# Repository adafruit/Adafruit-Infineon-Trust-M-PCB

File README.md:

## Adafruit Infineon Trust M Breakout Board PCB

<a href="http://www.adafruit.com/products/4351"><br/>
Click here to purchase one from the Adafruit shop</a>

PCB files for the Adafruit Infineon Trust M Breakout Board. 

Format is EagleCAD schematic and board layout
* https://www.adafruit.com/product/4351

### Description

This is a STEMMA I2C breakout for the Infineon OPTIGA TRUST M SLS 32AIA.

OPTIGA Trust M is the next generation of Trust X. OPTIGA Trust M brings RSA 1K/2K + ECC256/384.

A crypto authentication chip much like the ATECC608 STEMMA we put into the shop last week, but with: ECC NIST P256/P384, SHA-256, TRNG, DRNG, RSA® 1024/2048 and 4.5K of user memory.

This chip can store your private keys securely, as well as generate true random numbers, which is what we’ve got going on in this demo below. Check out https://github.com/Infineon/optiga-trust-m for the Arduino library

Comes with a bit of 0.1" standard header in case you want to use it with a breadboard or perfboard.  Four 2.5mm (0.1") mounting holes for easy attachment. Clear Padlock and STEMMA QT cable not included (but we have them in the shop). One board per order.

### License

Adafruit invests time and resources providing this open source design, please support Adafruit and open-source hardware by purchasing products from [Adafruit](https://www.adafruit.com)!

Designed by Limor Fried/Ladyada for Adafruit Industries.

Creative Commons Attribution/Share-Alike, all text above must be included in any redistribution. 
See license.txt for additional details.

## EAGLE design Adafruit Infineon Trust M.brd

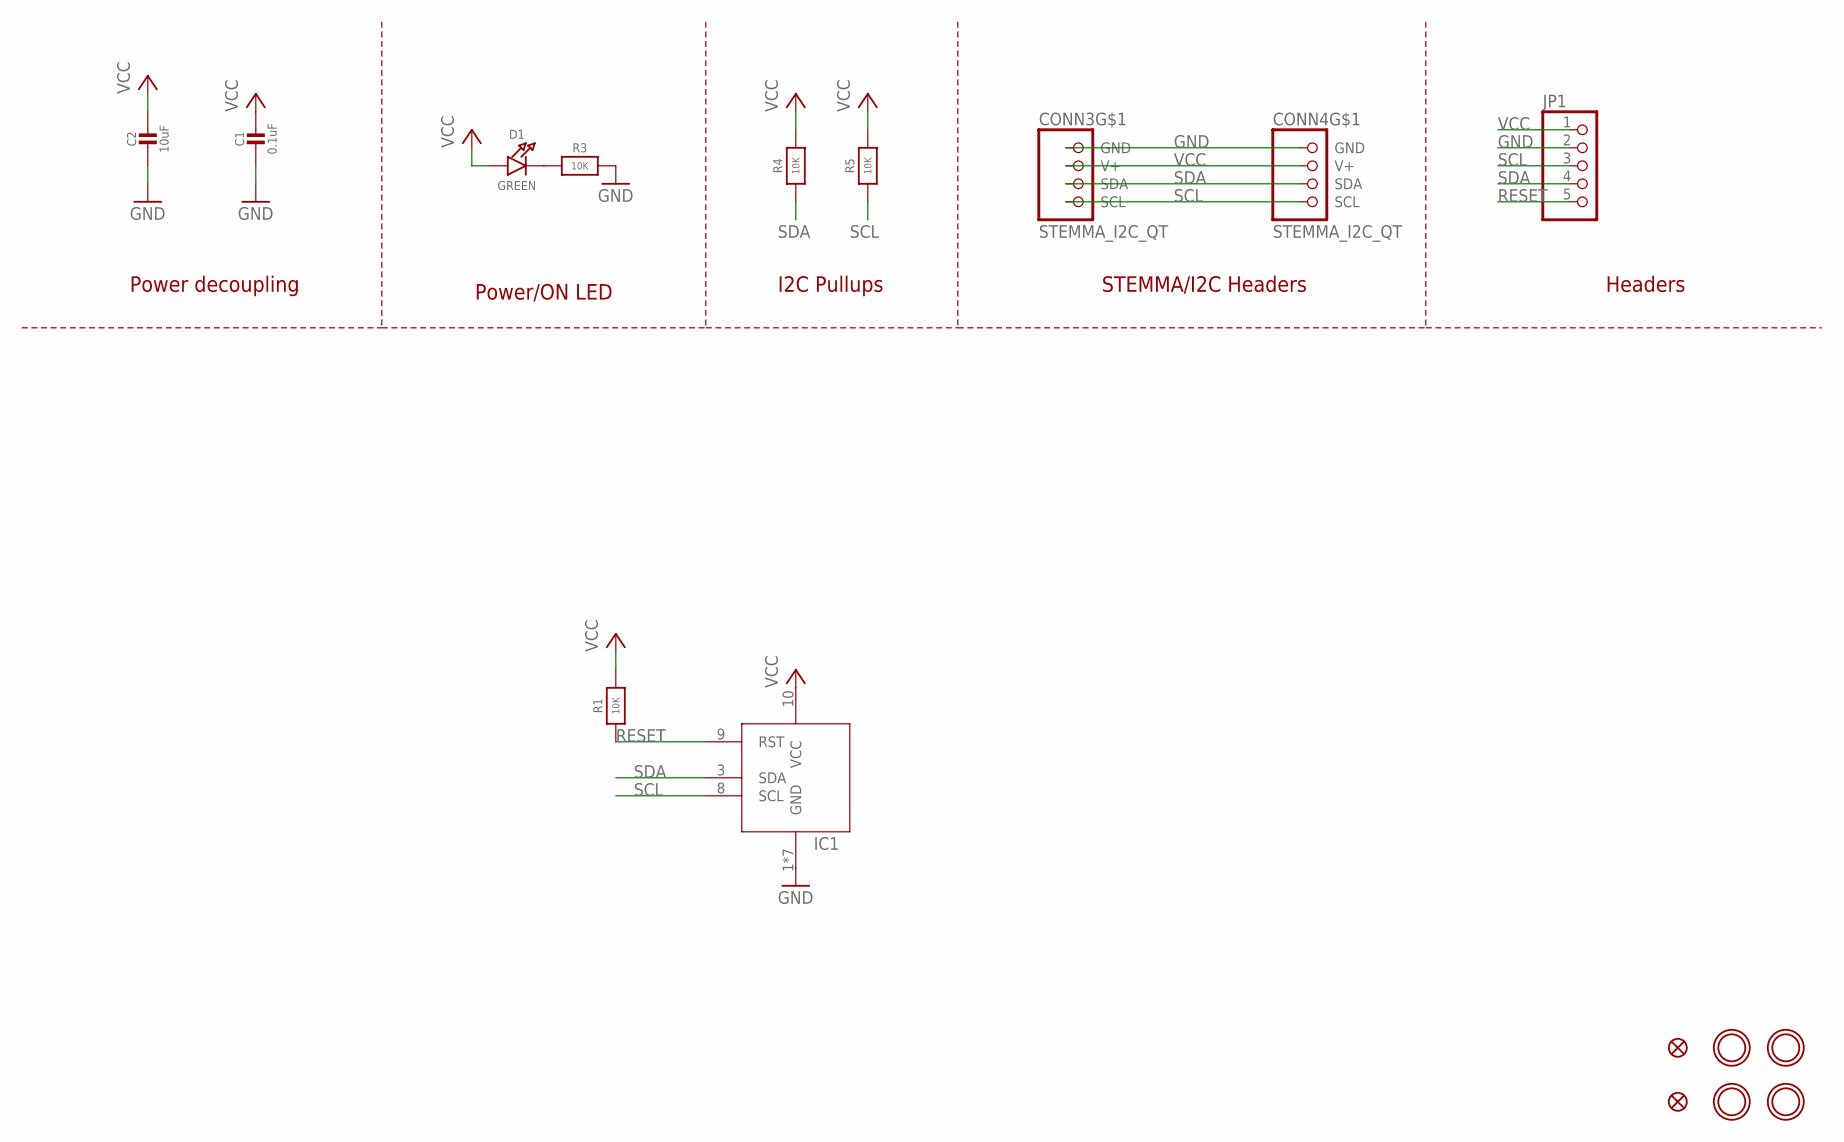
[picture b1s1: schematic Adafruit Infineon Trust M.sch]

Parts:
C1: 0.1uF; 0603-NO
C2: 10uF; 0805-NO
CONN3, CONN4: STEMMA_I2C_QT; JST_SH4
D1: GREEN; CHIPLED_0603_NOOUTLINE
FID3, FID4: FIDUCIAL_1MM
IC1: OPTIGA_TRUST_X; PG-USON10-10-2
JP1: HEADER-1X570MIL; 1X05_ROUND_70
R1, R3, R4, R5: 10K; 0603-NO
U$11, U$12, U$14, U$15: MOUNTINGHOLE2.5; MOUNTINGHOLE_2.5_PLATED

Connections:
GND: C1.2, C2.2, CONN3.1 (GND), CONN4.1 (GND), IC1.1 (GND), IC1.2 (GND), IC1.4 (GND), IC1.5 (GND), IC1.6 (GND), IC1.7 (GND), IC1.THERM (GND), JP1.2, R3.2
unnamed: D1.C, R3.1
RESET: IC1.9 (RST), JP1.5, R1.1
SCL: CONN3.4 (SCL), CONN4.4 (SCL), IC1.8 (SCL), JP1.3, R5.1
SDA: CONN3.3 (SDA), CONN4.3 (SDA), IC1.3 (SDA), JP1.4, R4.1
VCC: C1.1, C2.1, CONN3.2 (V+), CONN4.2 (V+), D1.A, IC1.10 (VCC), JP1.1, R1.2, R4.2, R5.2

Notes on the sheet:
Power/ON LED
Power decoupling
I2C Pullups
STEMMA/I2C Headers
Headers

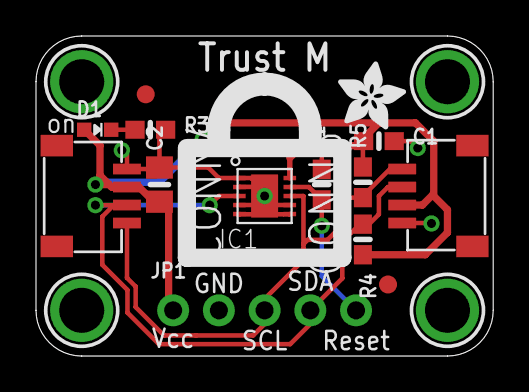
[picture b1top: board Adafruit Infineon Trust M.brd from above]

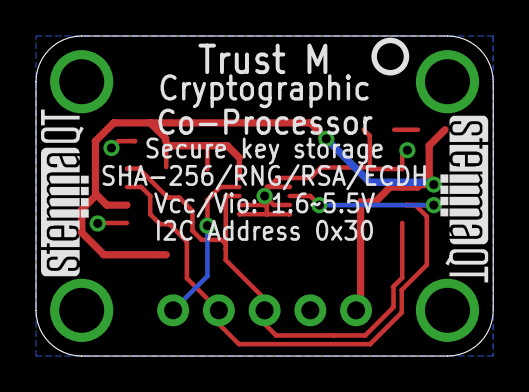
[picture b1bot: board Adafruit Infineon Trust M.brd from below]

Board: 2 copper layers, 25.4 x 17.8 mm, 21 parts (3 on the bottom side), 6 nets.

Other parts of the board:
U$17: ADAFRUIT_3.5MM
U$18: PCBFEAT-REV-040
U$19, U$20: STEMMAQT

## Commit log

2022-07-08 Added PCB files

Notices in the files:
parts and their libraries:
microbuilder: This work is placed in the public domain, and may be freely used for commercial and non-commercial work with the following conditions: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
